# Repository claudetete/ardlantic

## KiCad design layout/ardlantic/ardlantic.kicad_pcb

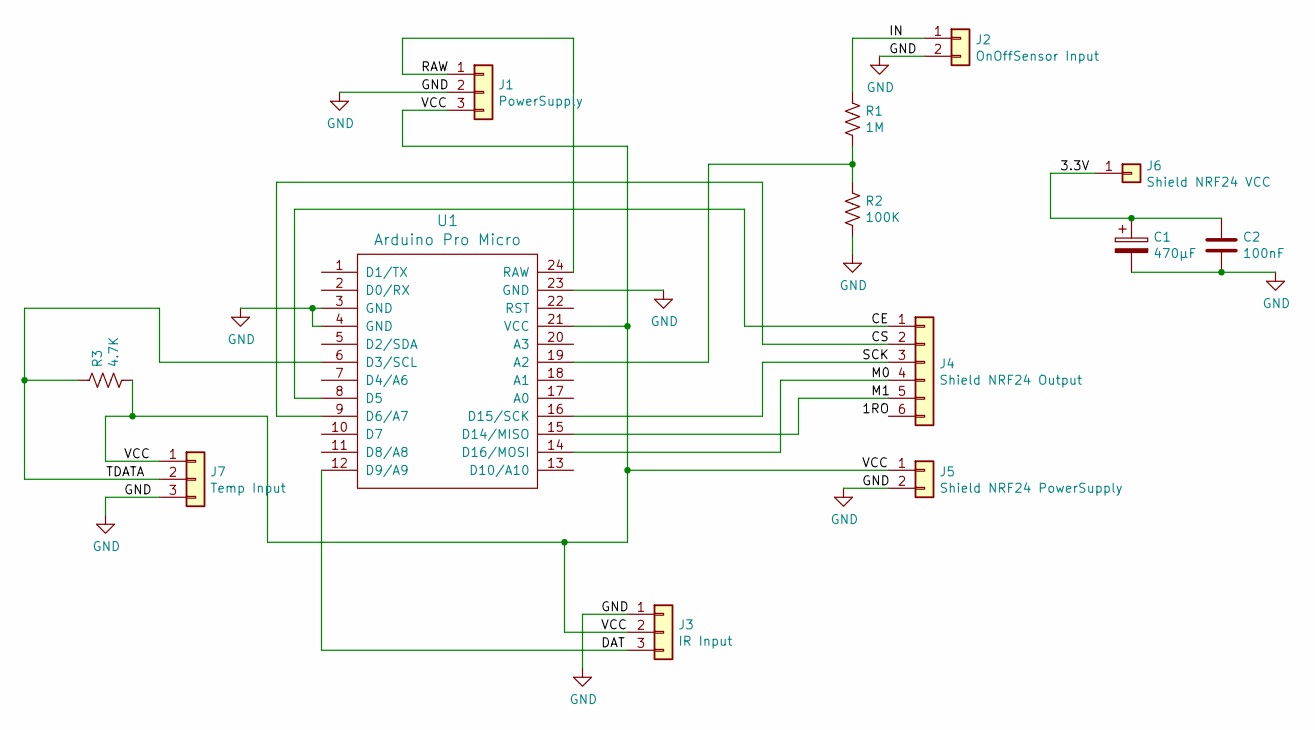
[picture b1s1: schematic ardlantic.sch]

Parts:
C1: 470µF; CP_Radial_D10.0mm_P5.00mm
C2: 100nF; CP_Radial_D5.0mm_P2.50mm
J1: PowerSupply; PinHeader_1x03_P2.54mm_Vertical
J2: OnOffSensor Input; PinHeader_1x02_P2.54mm_Vertical
J3: IR Input; PinHeader_1x03_P2.54mm_Vertical
J4: Shield NRF24 Output; PinHeader_1x06_P2.54mm_Vertical
J5: Shield NRF24 PowerSupply; PinHeader_1x02_P2.54mm_Vertical
J6: Shield NRF24 VCC; PinHeader_1x01_P2.54mm_Vertical
J7: Temp Input; PinHeader_1x03_P2.54mm_Vertical
R1: 1M; R_Axial_DIN0207_L6.3mm_D2.5mm_P10.16mm_Horizontal
R2: 100K; R_Axial_DIN0207_L6.3mm_D2.5mm_P10.16mm_Horizontal
R3: 4.7K; R_Axial_DIN0207_L6.3mm_D2.5mm_P10.16mm_Horizontal
U1: Arduino Pro Micro; ProMicro

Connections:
/3.3V: C1.1, C2.1, J6.1
/CE: J4.1, U1.8 (D5)
/CS: J4.2, U1.9 (D6/A7)
/DAT: J3.3, U1.12 (D9/A9)
/IN: J2.1, R1.1
/M0: J4.4, U1.14 (D16/MOSI)
/M1: J4.5, U1.15 (D14/MISO)
/RAW: J1.1, U1.24 (RAW)
/SCK: J4.3, U1.16 (D15/SCK)
/TDATA: J7.2, R3.1, U1.6 (D3/SCL)
/VCC: J1.3, J3.2, J5.1, J7.1, R3.2, U1.21 (VCC)
GND: C1.2, C2.2, J1.2, J2.2, J3.1, J5.2, J7.3, R2.2, U1.3 (GND), U1.4 (GND), U1.23 (GND)
unnamed: R1.2, R2.1, U1.19 (A2)

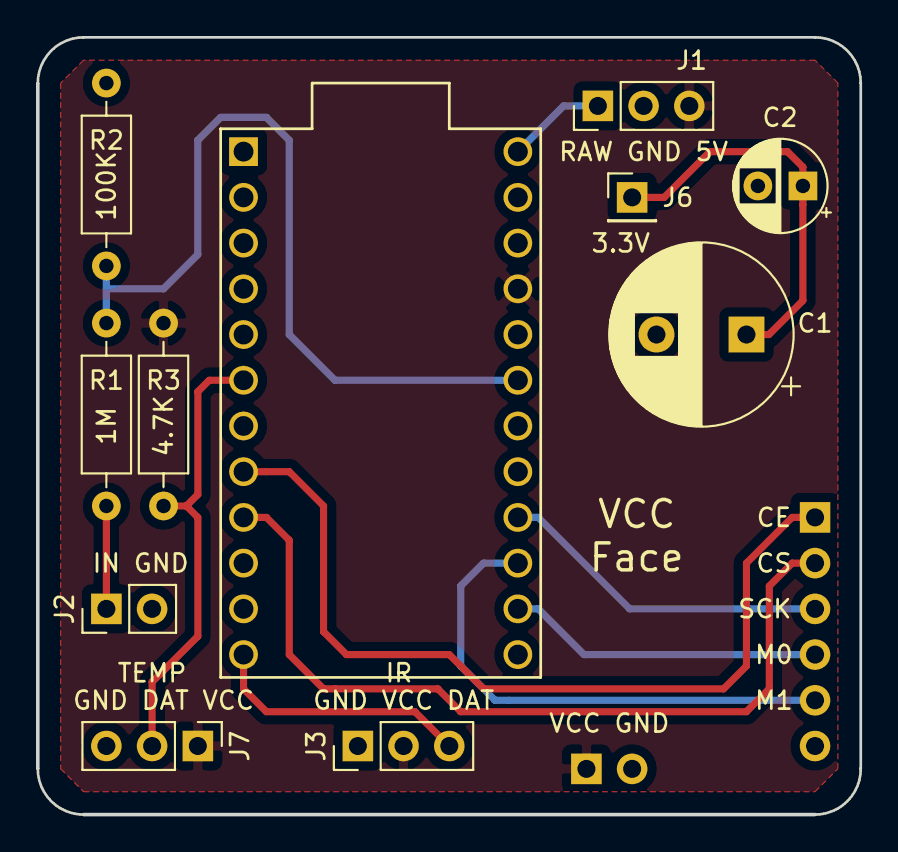
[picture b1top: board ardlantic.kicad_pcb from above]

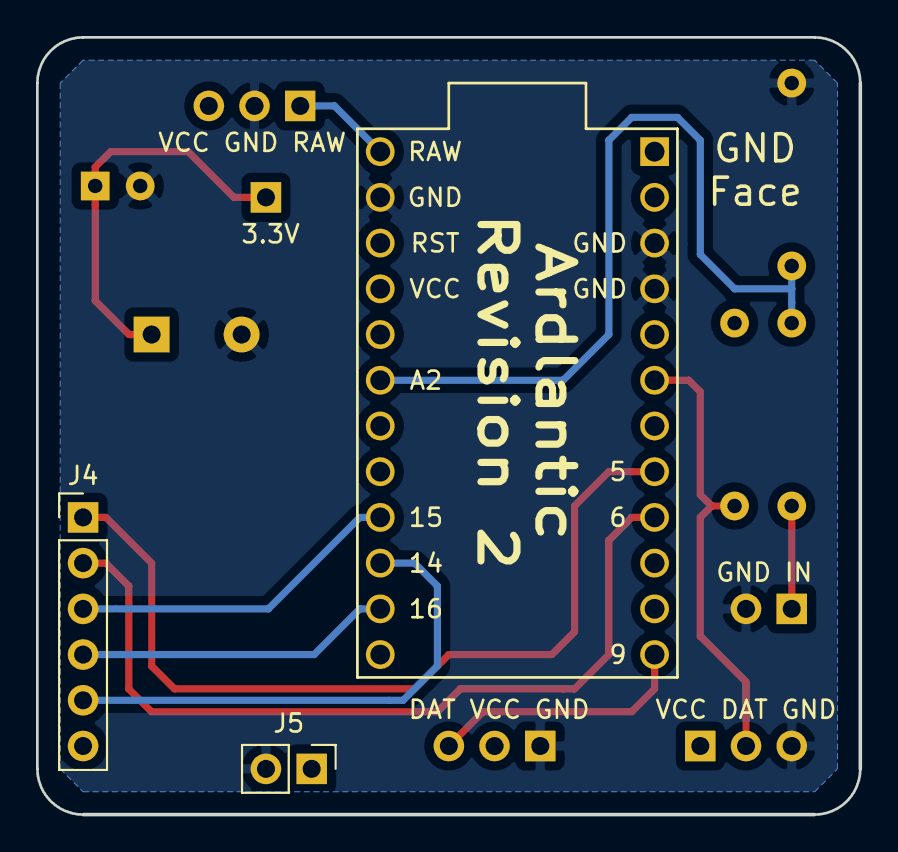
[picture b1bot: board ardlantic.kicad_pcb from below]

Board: 2 copper layers, 45.7 x 43.2 mm, 13 parts (2 on the bottom side), 13 nets.

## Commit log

2017-10-02 init repo with current project, useful to work on multiple computer
2017-10-17 implementation of MySensors in sketch (presentation, reception OK) + some test sketch + update lib for ardlantic about IR; FIXME crash during send of IR frame
2017-10-20 add debug print
2018-12-22 Add missing command OFF + make not boolean value work + Pin A2 to read HVAC power + dzvents script for Domoticz + fix problem in Ardlantic lib
2019-03-10 add first layout design
2020-04-01 New layout revision with fix + fix mysensor pin + add temperature sensor
2020-04-02 differentiate multiple nodes with same features
